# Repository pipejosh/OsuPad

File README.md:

**Osu / Geometry dash pad**

This project is a little  pad for geomeotry dash or osu (or any other rithm game that includes tappin a mouse or keyboard), this little pad has 3 keys, that can be programmed to be anything, in this case they are programmed to be Z, X, and W, it also has a oled screen, that has stadistic, like the current hour

I made this project because I felt like it was time to jump from keyboard to this little pad, I was orignally gonna buy one, but what a better opportunity to learn how to make one myself.

### Pcb Image

### Case 3d model

### Schematic pcb

### BOM

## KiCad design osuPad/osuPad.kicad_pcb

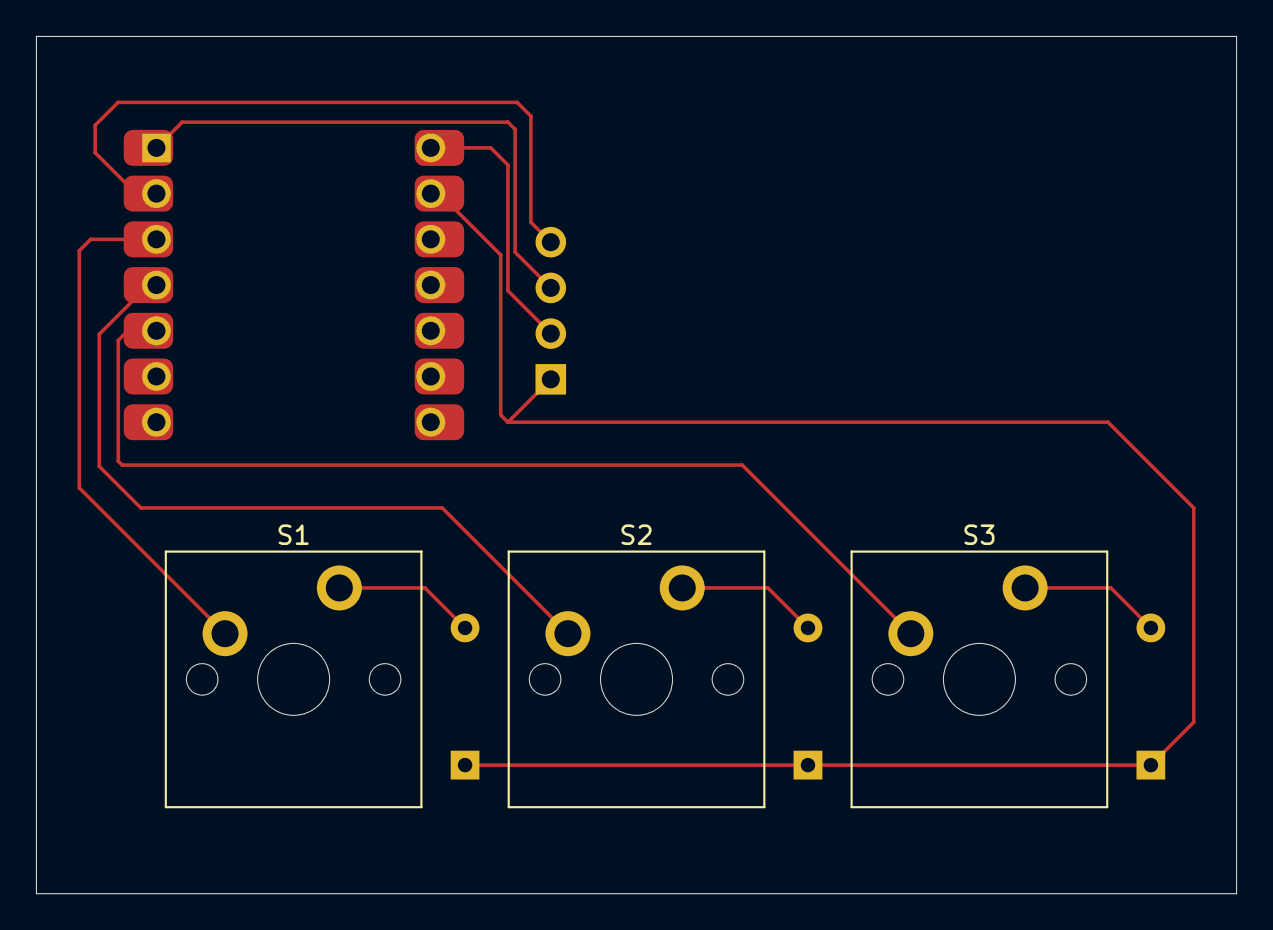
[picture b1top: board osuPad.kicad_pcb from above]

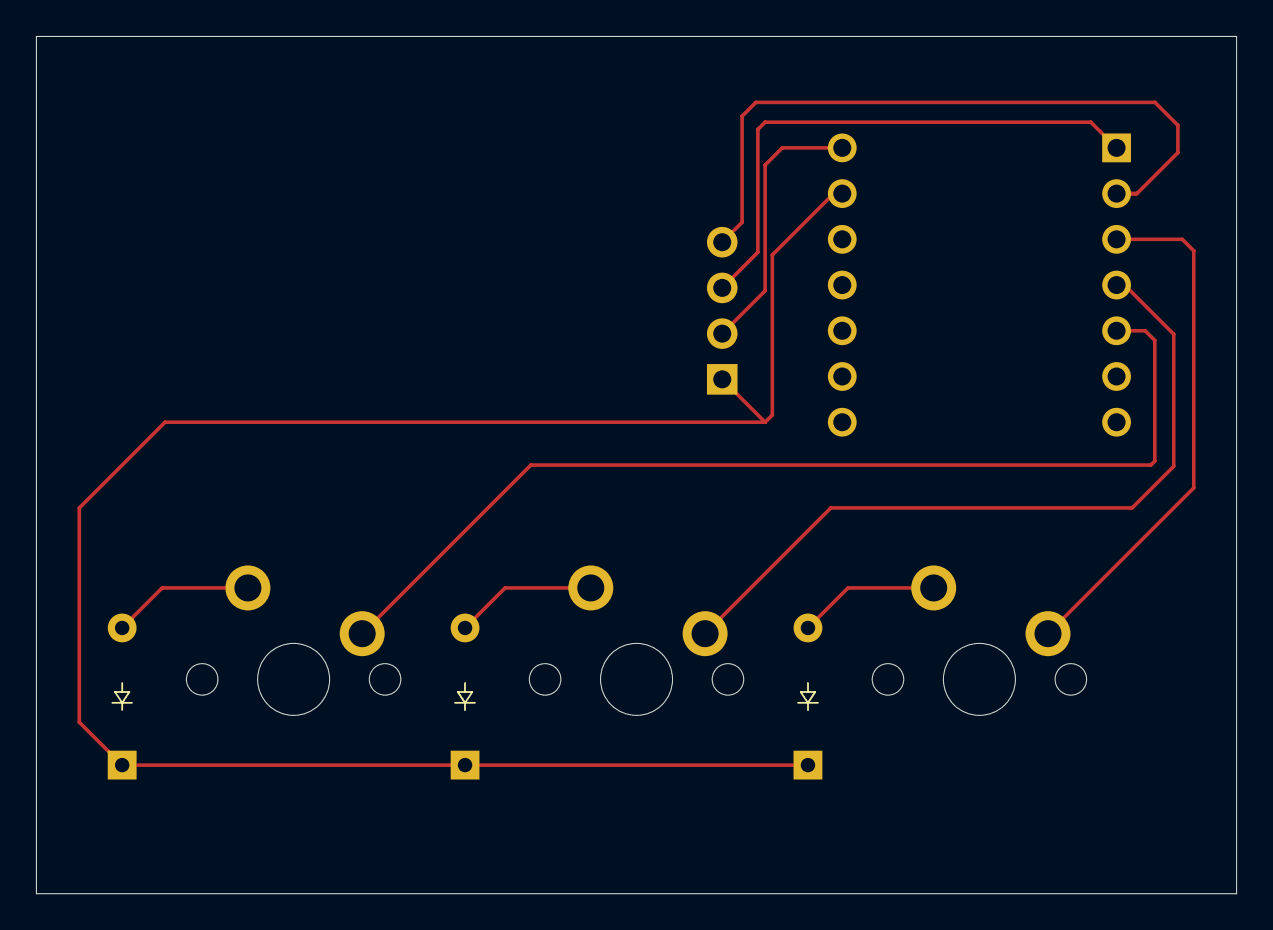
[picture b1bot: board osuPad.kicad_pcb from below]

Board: 2 copper layers, 66.7 x 47.6 mm, 8 parts (3 on the bottom side), 10 nets.

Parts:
D1, D2, D3: Diode_DO-35
J1: OLED_128x32
S1, S2, S3: MX_PCB_1.00u
U1: MCU_Seeed_XIAO_RP2040; Seeed_XIAO_RP2040

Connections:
unnamed: D1.2 (A), S1.2
unnamed: D1.1 (K), D2.1 (K), D3.1 (K), J1.1 (GND), U1.13 (GND)
unnamed: D2.2 (A), S2.2
unnamed: D3.2 (A), S3.2
unnamed: J1.3 (SCL), U1.1 (PA02_A0_D0)
unnamed: J1.4 (SDA), U1.2 (PA4_A1_D1)
unnamed: J1.2 (VCC), U1.14 (5V)
unnamed: S3.1, U1.5 (PA8_A4_D4_SDA)
unnamed: S1.1, U1.3 (PA10_A2_D2)
unnamed: S2.1, U1.4 (PA11_A3_D3)

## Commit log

2025-11-30 create the pcb with the schematics
    3 switches, 1 oled screen and the seed
2025-11-30 add BOM
